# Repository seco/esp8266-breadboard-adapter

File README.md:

# esp8266-01 breadboard adapter
Adapter for esp8266-01 module to the breadboard.

*Designed by fu*

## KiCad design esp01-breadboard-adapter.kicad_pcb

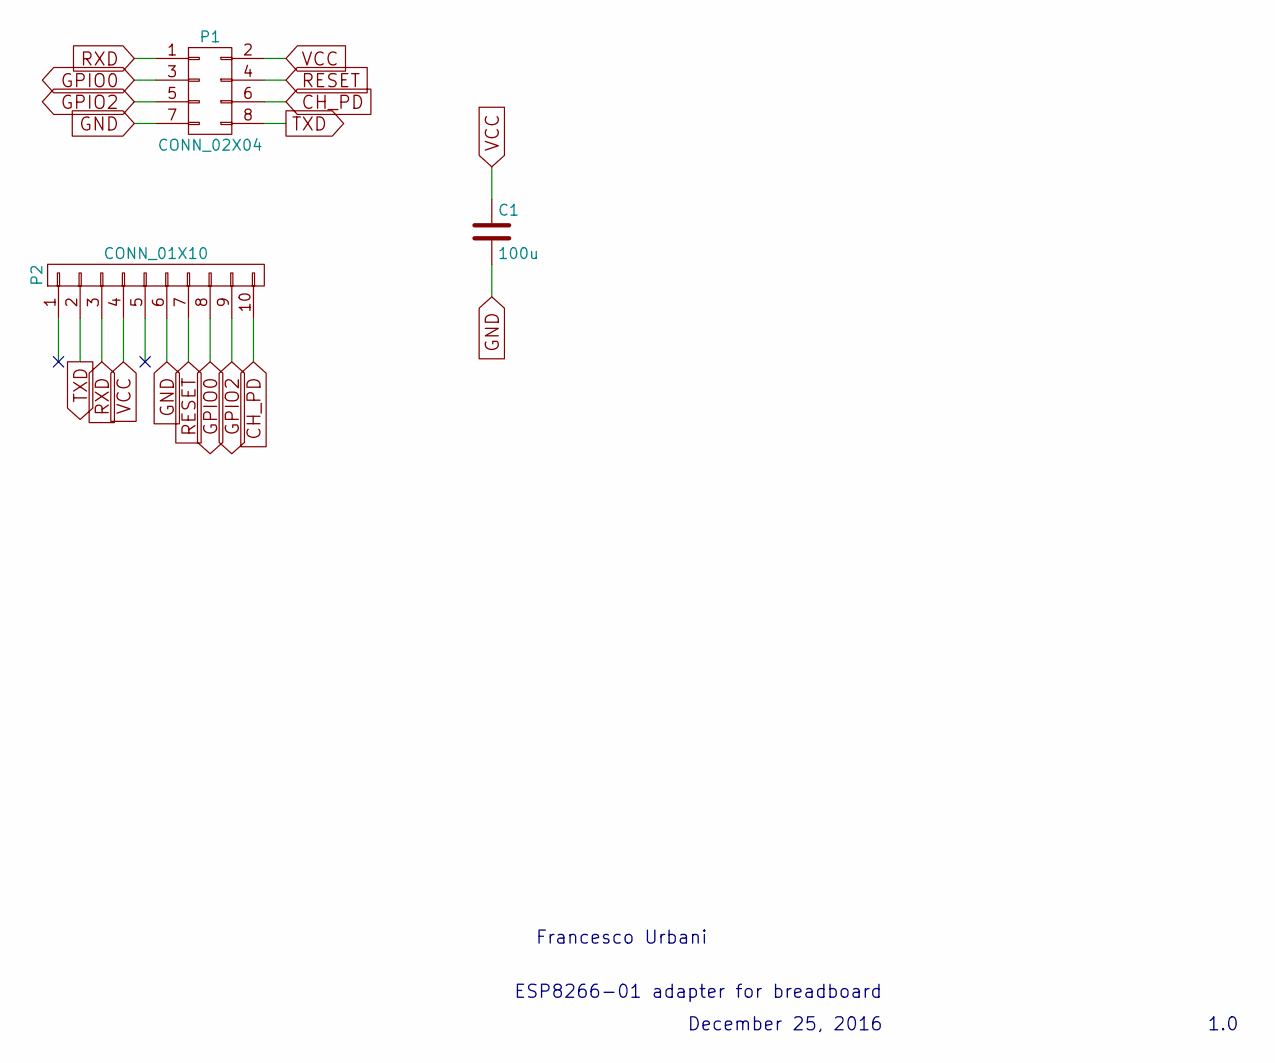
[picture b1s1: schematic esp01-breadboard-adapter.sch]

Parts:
C1: 100u; C_1206
P1: CONN_02X04; Pin_Header_Straight_2x04
P2: CONN_01X10; Pin_Header_Straight_1x10_Pitch2.54mm

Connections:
CH_PD: P1.6, P2.10
GND: C1.2, P1.7, P2.6
GPIO0: P1.3, P2.8
GPIO2: P1.5, P2.9
RESET: P1.4, P2.7
RXD: P1.1, P2.3
TXD: P1.8, P2.2
VCC: C1.1, P1.2, P2.4

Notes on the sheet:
ESP8266-01 adapter for breadboard
December 25, 2016
1.0
Francesco Urbani

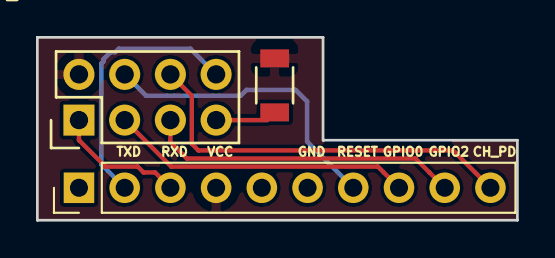
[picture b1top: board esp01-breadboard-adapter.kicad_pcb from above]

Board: 2 copper layers, 26.7 x 10.2 mm, 3 parts (0 on the bottom side), 8 nets.

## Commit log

2016-12-25 added netlist
2016-12-25 parts placed on pcb
2016-12-25 added cap to schematic
2016-12-25 begin 2nd layer pcb
2016-12-25 pcb almost finished
2016-12-26 pcb faces ok
2016-12-26 pcb finished
2016-12-26 pcb finished, added copper pour on both layers
2016-12-26 added images
2016-12-27 edited edge cuts
2016-12-27 added led on gpio2
2016-12-27 pcb complete
    pcb complete with signed bottom sikscreen
2016-12-27 plot
2016-12-27 img added
2016-12-27 missing footprint 10 pin header
2016-12-27 edited schematic
2016-12-28 new pcb layout, fix connection
2016-12-28 pcb complete
2016-12-28 added front silkscreen
2016-12-28 updated img
2016-12-28 updated img and silkscreen
2016-12-28 slightly updated pcb
2016-12-28 renamed img
2017-01-21 eagle version
2017-01-22 board done
2017-01-22 updated board
2017-01-22 added docs
2017-01-25 minor fix
2017-01-26 redefined board
2017-01-29 changed header
